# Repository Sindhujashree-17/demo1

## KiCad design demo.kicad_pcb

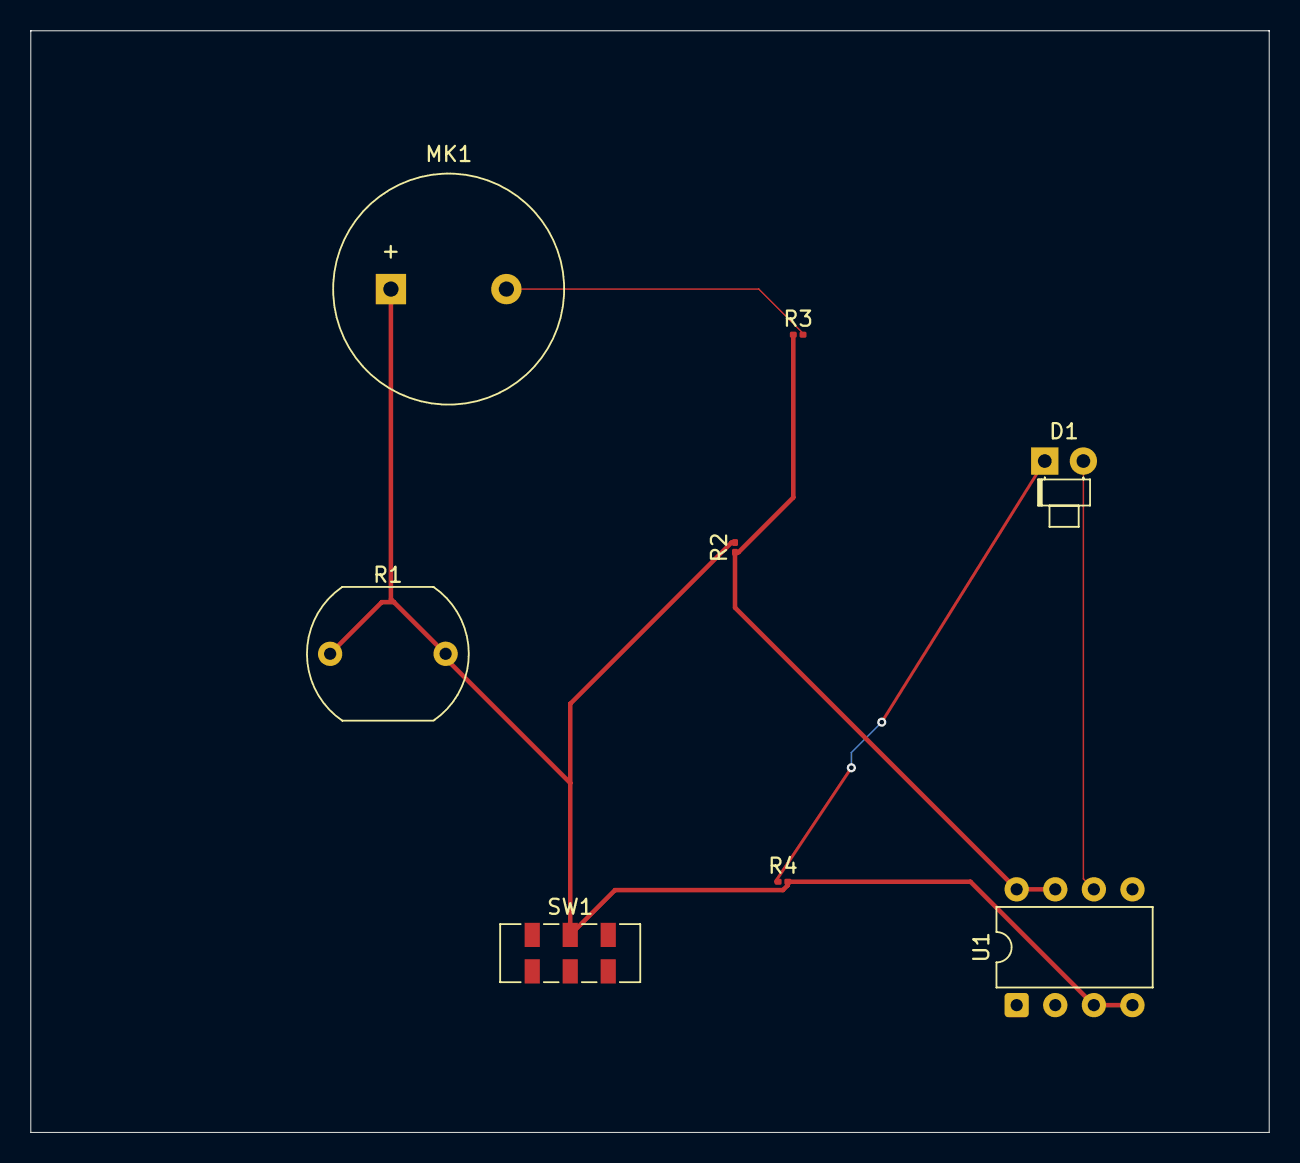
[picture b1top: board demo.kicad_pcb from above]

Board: 2 copper layers, 81.5 x 72.5 mm, 9 parts (0 on the bottom side), 5 nets.

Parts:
BT1: Battery_Cell; Battery_CR1225
D1: LED; LED_D1.8mm_W1.8mm_H2.4mm_Horizontal_O1.27mm_Z1.6mm
MK1: Microphone_Condenser; Buzzer_15x7.5RM7.6
R1: LDR03; R_LDR_10x8.5mm_P7.6mm_Vertical
R2, R3, R4: R; R_0201_0603Metric
SW1: SW_DPDT_x2; SW_DPDT_CK_JS202011JCQN
U1: ATtiny85-20P; DIP-8_W7.62mm

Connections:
+3.3V: R2.1, R3.1, U1.7 (PB2), U1.8 (VCC)
/LED: D1.2 (A), U1.6 (PB1)
GND: MK1.1 (-), R1.1, R1.2, R2.2, R4.2, SW1.2 (B), U1.3 (XTAL2/PB4), U1.4 (GND)
unnamed: D1.1 (K), R4.1
unnamed: MK1.2 (+), R3.2

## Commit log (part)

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2025-01-30 num = 6
    factorial = 1
    for i in range(1, num + 1):
    factorial *= i
    print(f"The factorial of {num} is {factorial}"
